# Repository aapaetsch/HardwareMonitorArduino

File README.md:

## Rough Overview of the project so far:
- Desktop Hardware Monitor: Contains the PCB Files for the project.
- Hardware_Monitor: Contains the arduino code for an arduino microcontroller, currently this is an ATMEGA328p-pu. 
  - This will be used to drive 6x7 segment displays (common cathode) and (hopefully) 2 i2c 128X64px screens.
  - Drivers for the I2C displays still need to be coded.
  - Some logic from the output pins will need to be offloaded to external IC chips
    - So far 74HC164 8-bit Shift Register, 74LS04 hex inverter, 74LS138 
  - Serial inverters are bulky, maybe V-USB if the chip has enough storage after the program is close to finished in size...
- HardwareMonitorArduino: Contains the code related to a C# program that will run on the host pc. (Incomplete) Will share code with my DesktopHardwareMonitor electron application.

V1 PCB - No Input USB and requires a redesign as it does not fit in the 100mm x 100mm limit for JLPCB

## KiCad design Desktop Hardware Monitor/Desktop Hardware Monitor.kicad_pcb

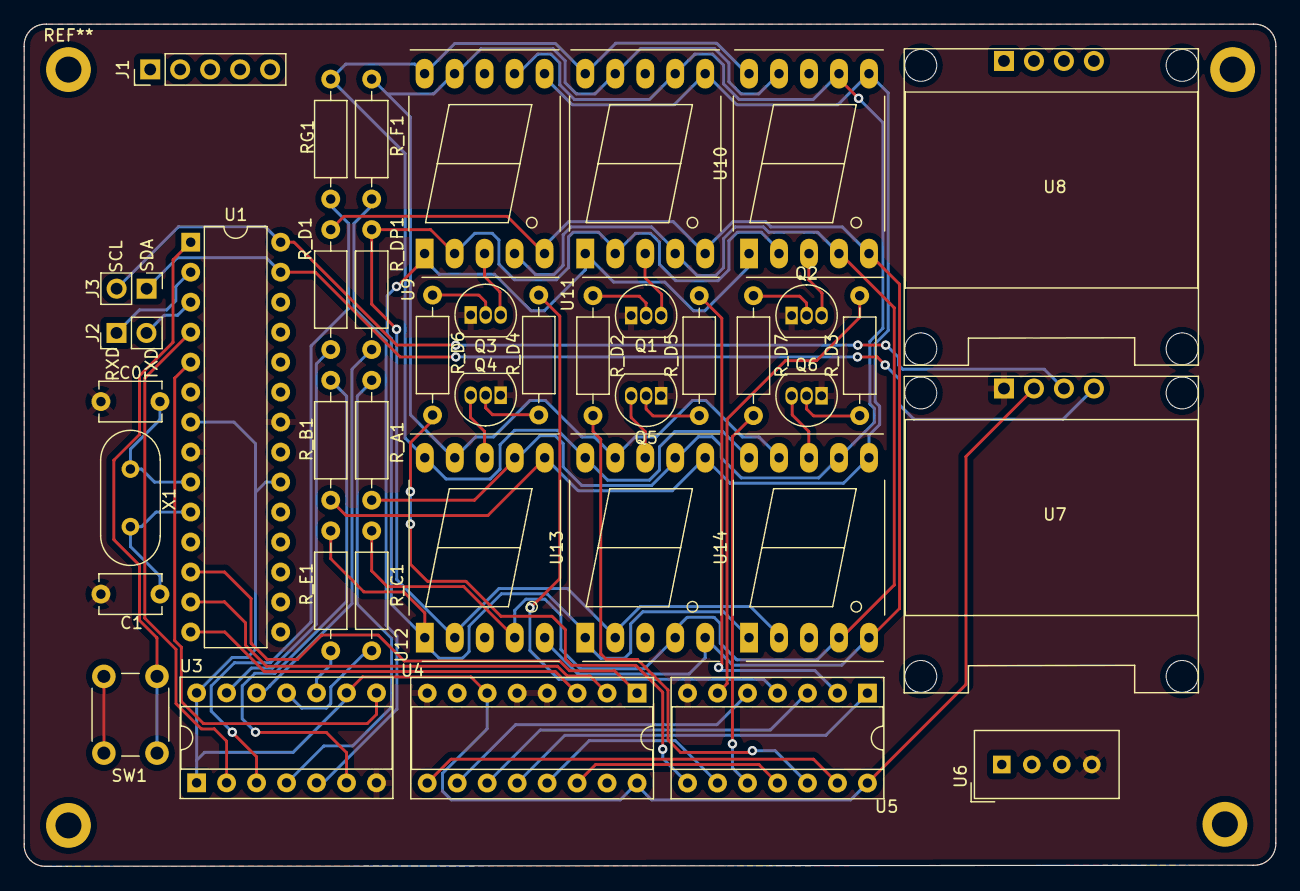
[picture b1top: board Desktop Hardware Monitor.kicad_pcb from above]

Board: 2 copper layers, 106.0 x 71.3 mm, 40 parts (0 on the bottom side), 54 nets.

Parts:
C0, C1: 22pf; C_Disc_D5.1mm_W3.2mm_P5.00mm
J1: USB_C_Receptacle_USB2.0; PinHeader_1x05_P2.54mm_Vertical
J2, J3: Conn_01x02_Female; PinHeader_1x02_P2.54mm_Vertical
Q1, Q2, Q3, Q4, Q5, Q6: 2N3904; TO-92_Inline
RG1: 1K; R_Axial_DIN0207_L6.3mm_D2.5mm_P10.16mm_Horizontal
R_A1: 1K; R_Axial_DIN0207_L6.3mm_D2.5mm_P10.16mm_Horizontal
R_B1: 1K; R_Axial_DIN0207_L6.3mm_D2.5mm_P10.16mm_Horizontal
R_C1: 1K; R_Axial_DIN0207_L6.3mm_D2.5mm_P10.16mm_Horizontal
R_D1, R_D2, R_D3, R_D4, R_D5, R_D6, R_D7: 1K; R_Axial_DIN0207_L6.3mm_D2.5mm_P10.16mm_Horizontal
R_DP1: 1K; R_Axial_DIN0207_L6.3mm_D2.5mm_P10.16mm_Horizontal
R_E1: 1K; R_Axial_DIN0207_L6.3mm_D2.5mm_P10.16mm_Horizontal
R_F1: 1K; R_Axial_DIN0207_L6.3mm_D2.5mm_P10.16mm_Horizontal
SW1: Reset Switch; SW_PUSH_6mm_H4.3mm
U1: ATmega328-P; DIP-28_W7.62mm
U3: 74HC164; DIP-14_W7.62mm_Socket
U4: 74LS138; DIP-16_W7.62mm_Socket
U5: 74LS04; DIP-14_W7.62mm_Socket
U6: DHT11; Aosong_DHT11_5.5x12.0_P2.54mm
U7, U8: SSD1306; IC2_Display_4_Pin
U9, U10, U11, U12, U13, U14: SM420561N; 7SegmentLED_LTS6760_LTS6780
X1: XTAL; Crystal_HC49-4H_Vertical

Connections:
A: R_A1.1, U3.4 (Q1)
A0: U1.12 (PD6), U4.1 (A0)
A1: U1.13 (PD7), U4.2 (A1)
A2: U1.14 (PB0), U4.3 (A2)
B: R_B1.1, U3.6 (Q3)
C: R_C1.1, U3.11 (Q5)
CLK: U1.5 (PD3), U3.8 (CLK)
D: R_D1.1, U3.12 (Q6)
DP: R_DP1.1, U3.13 (Q7)
DSB: U1.4 (PD2), U3.2 (DSB)
Digit1: Q1.3 (C), U11.3 (CC)
Digit2: Q2.3 (C), U10.3 (CC)
Digit3: Q3.3 (C), U9.3 (CC)
Digit4: Q4.3 (C), U12.8 (CC)
Digit5: Q5.3 (C), U13.8 (CC)
Digit6: Q6.3 (C), U14.8 (CC)
E: R_E1.1, U3.10 (Q4)
F: R_F1.1, U3.5 (Q2)
G: RG1.1, U3.3 (Q0)
GND: C0.2, C1.2, Q1.1 (E), Q2.1 (E), Q3.1 (E), Q4.1 (E), Q5.1 (E), Q6.1 (E), SW1.2, U1.8 (GND), U1.22 (GND), U3.7 (GND), U4.4 (E1), U4.5 (E2), U4.8 (GND), U5.7 (GND), U6.4 (GND), U7.1 (C2P)
unnamed: Q1.2 (B), R_D2.1
unnamed: Q2.2 (B), R_D7.1
unnamed: Q3.2 (B), R_D6.1
unnamed: Q4.2 (B), R_D4.1
unnamed: Q5.2 (B), R_D5.1
unnamed: Q6.2 (B), R_D3.1
unnamed: RG1.2, U9.10 (G), U10.10 (G), U11.10 (G), U12.10 (G), U13.10 (G), U14.10 (G)
unnamed: R_A1.2, U9.7 (A), U10.7 (A), U11.7 (A), U12.7 (A), U13.7 (A), U14.7 (A)
unnamed: R_B1.2, U9.6 (B), U10.6 (B), U11.6 (B), U12.6 (B), U13.6 (B), U14.6 (B)
unnamed: R_C1.2, U9.4 (C), U10.4 (C), U11.4 (C), U12.4 (C), U13.4 (C), U14.4 (C)
unnamed: R_D1.2, U9.2 (D), U10.2 (D), U11.2 (D), U12.2 (D), U13.2 (D), U14.2 (D)
unnamed: R_D2.2, U5.12
unnamed: R_D3.2, U5.6
unnamed: R_D4.2, U5.4
unnamed: R_D5.2, U5.2
unnamed: R_D6.2, U5.8
unnamed: R_D7.2, U5.10
unnamed: R_DP1.2, U9.5 (DP), U10.5 (DP), U11.5 (DP), U12.5 (DP), U13.5 (DP), U14.5 (DP)
unnamed: R_E1.2, U9.1 (E), U10.1 (E), U11.1 (E), U12.1 (E), U13.1 (E), U14.1 (E)
unnamed: R_F1.2, U9.9 (F), U10.9 (F), U11.9 (F), U12.9 (F), U13.9 (F), U14.9 (F)
unnamed: U4.9 (O6), U5.13
unnamed: U4.10 (O5), U5.5
unnamed: U4.11 (O4), U5.3
unnamed: U4.12 (O3), U5.1
unnamed: U4.13 (O2), U5.9
unnamed: U4.14 (O1), U5.11
RST: SW1.1, U1.1 (~RESET/PC6)
RXD: J2.1, U1.2 (PD0)
SCL: J3.2, U1.28 (PC5), U7.3 (C1P)
SDA: J3.1, U1.27 (PC4), U7.4 (C1N)
TXD: J2.2, U1.3 (PD1)
VCC: U1.7 (VCC), U1.20 (AVCC), U3.1 (DSA), U3.9 (~CLR), U3.14 (VCC), U4.6 (E3), U4.16 (VCC), U5.14 (VCC), U6.1 (VCC), U7.2 (C2N)
XTAL1: C0.1, U1.9 (XTAL1/PB6), X1.1
XTAL2: C1.1, U1.10 (XTAL2/PB7), X1.2

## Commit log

2022-11-19 Initial commit, this contains the start of the code for driving the arduino and the rough windows app to get hardware data from the pc
2022-11-19 Commit kicad files
2022-11-23 Add start of arduino side of project
2022-11-23 Start switch to using LibreHardwareMonitor instead of open hardware monitor
    - OpenHardwareMonitor was missing the vast majority of sensors, only working on the gpu and partially on the cpu
2022-11-23 Update C# side of project
2022-11-23 Update PCB Files
2022-11-24 Update 7 segment driver code to use a separate class
